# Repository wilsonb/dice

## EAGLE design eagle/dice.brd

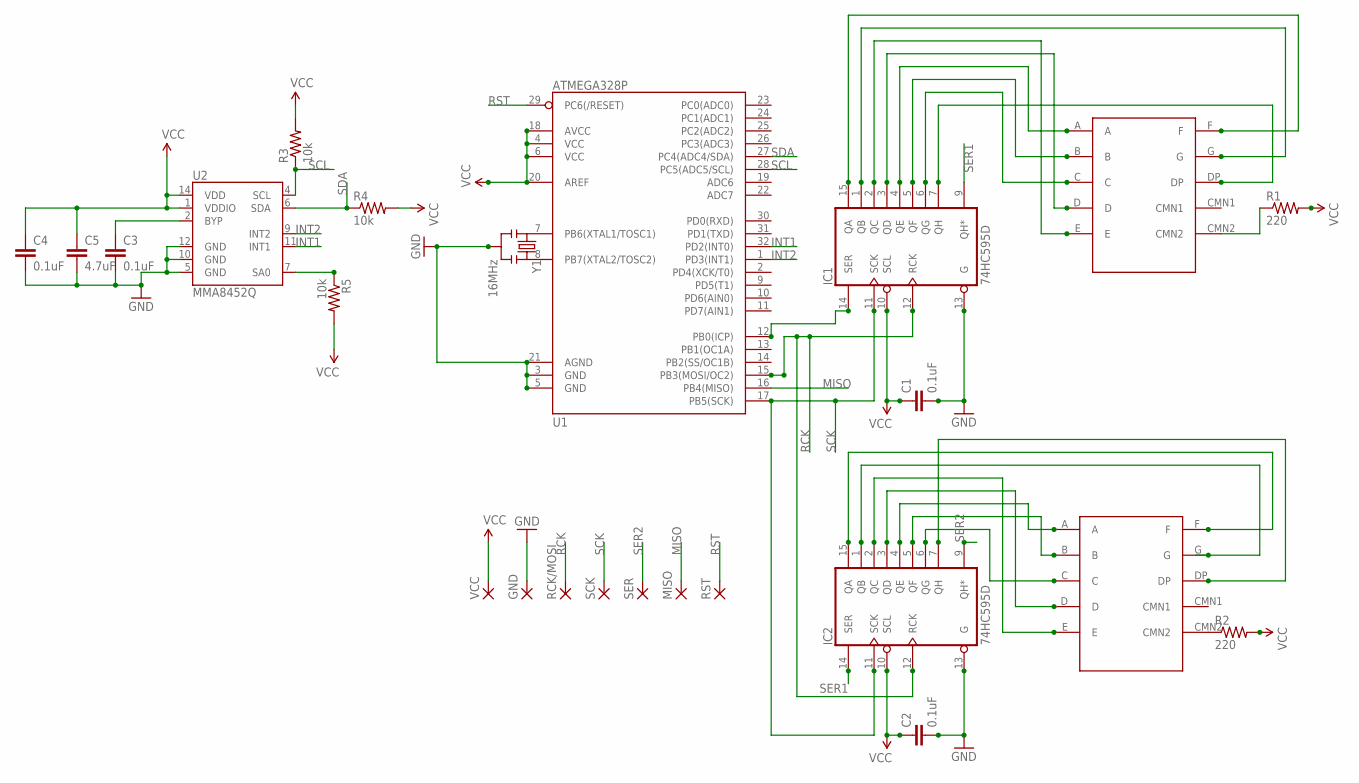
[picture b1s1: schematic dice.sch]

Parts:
C1, C2, C3, C4: 0.1uF; 0402-CAP
C5: 4.7uF; 0402-CAP
GND: 1,6/0,8
IC1, IC2: 74HC595D; SO16
MISO: 1,6/0,8
R1, R2: 220; 0603-RES
R3, R4, R5: 10k; 0402-RES
RCK/MOSI: 1,6/0,8
RST: 1,6/0,8
SCK: 1,6/0,8
SER: 1,6/0,8
U1: ATMEGA328P; TQFP32-08
U2: MMA8452Q; QFN-16_0.5MM
U$1, U$2: LUMEXSMHTA5604RISIT; 7SEG-10SMD
VCC: 1,6/0,8
Y1: 16MHz; RESONATOR-SMD

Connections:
GND: C1.2, C2.2, C3.2, C4.2, C5.2, GND.1, IC1.8 (GND), IC1.13 (G), IC2.8 (GND), IC2.13 (G), U1.3 (GND), U1.5 (GND), U1.21 (AGND), U2.5 (GND), U2.10 (GND), U2.12 (GND), Y1.2
INT1: U1.32 (PD2(INT0)), U2.11 (INT1)
INT2: U1.1 (PD3(INT1)), U2.9 (INT2)
MISO: MISO.1, U1.16 (PB4(MISO))
unnamed: R1.1, U$1.CMN2
unnamed: IC1.4 (QE), U$1.A
unnamed: IC1.14 (SER), U1.12 (PB0(ICP))
unnamed: U1.8 (PB7(XTAL2/TOSC2)), Y1.3
unnamed: U1.7 (PB6(XTAL1/TOSC1)), Y1.1
unnamed: IC1.15 (QA), U$1.F
unnamed: IC1.1 (QB), U$1.G
unnamed: IC1.2 (QC), U$1.E
unnamed: IC1.3 (QD), U$1.D
unnamed: IC1.5 (QF), U$1.B
unnamed: IC1.6 (QG), U$1.C
unnamed: IC1.7 (QH), U$1.DP
unnamed: R2.1, U$2.CMN2
unnamed: IC2.15 (QA), U$2.F
unnamed: IC2.1 (QB), U$2.G
unnamed: IC2.2 (QC), U$2.E
unnamed: IC2.3 (QD), U$2.D
unnamed: IC2.4 (QE), U$2.A
unnamed: IC2.5 (QF), U$2.B
unnamed: IC2.6 (QG), U$2.C
unnamed: IC2.7 (QH), U$2.DP
unnamed: R5.1, U2.7 (SA0)
unnamed: C3.1, U2.2 (BYP)
RCK: IC1.12 (RCK), IC2.12 (RCK), RCK/MOSI.1, U1.15 (PB3(MOSI/OC2))
RST: RST.1, U1.29 (PC6(/RESET))
SCK: IC1.11 (SCK), IC2.11 (SCK), SCK.1, U1.17 (PB5(SCK))
SCL: R3.1, U1.28 (PC5(ADC5/SCL)), U2.4 (SCL)
SDA: R4.1, U1.27 (PC4(ADC4/SDA)), U2.6 (SDA)
SER1: IC1.9 (QH*), IC2.14 (SER)
SER2: IC2.9 (QH*), SER.1
VCC: C1.1, C2.1, C4.1, C5.1, IC1.10 (SCL), IC1.16 (VCC), IC2.10 (SCL), IC2.16 (VCC), R1.2, R2.2, R3.2, R4.2, R5.2, U1.4 (VCC), U1.6 (VCC), U1.18 (AVCC), U1.20 (AREF), U2.1 (VDDIO), U2.14 (VDD), VCC.1

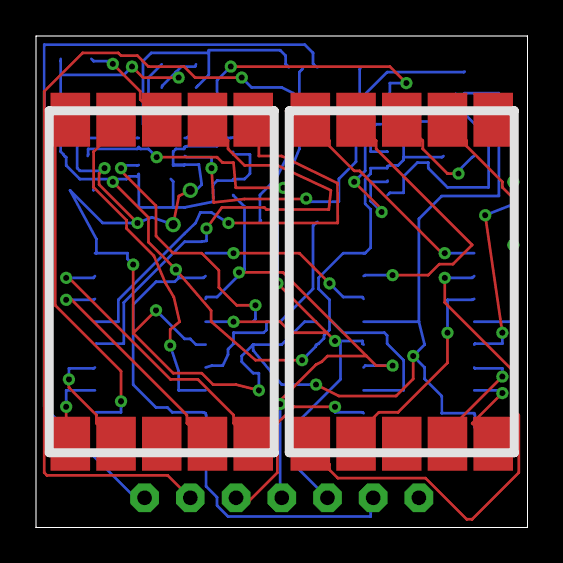
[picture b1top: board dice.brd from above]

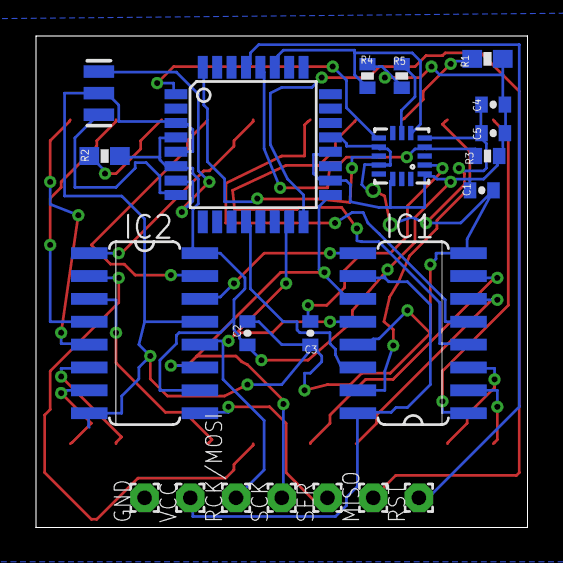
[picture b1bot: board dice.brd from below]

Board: 2 copper layers, 27.3 x 27.3 mm, 24 parts (22 on the bottom side), 35 nets.

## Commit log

2013-02-19 uploading files
2013-02-20 accelerometer triggers dice

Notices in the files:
parts and their libraries:
SparkFun-DigitalIC: Licensing: CC v3.0 Share-Alike You are welcome to use this library for commercial purposes.
